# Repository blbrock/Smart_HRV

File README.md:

# Smart HRV  
Smart HRV replaces OEM controllers for Carrier (and probably Venmar and other brand) Heat Recovery Ventilation  
units.  Smart HRV adds intelligence to system controls using indoor and outdoor sensors to montior humidity and  
to manage humidity, fresh air, and odor control optimal performance. Smart HRV also integrates with fan and dehumidifier  
controls on Nest thermostats.  The system consists of an arduino-based control unit, one or more indoor humidity sensors.  
An outdoor temperature and humidity sensor, and an android user interface app to provide monitoring and control of system   
functions.  
  
The current system is customized to our own application and will likely need modification for other applications. But the   
package includes basic serial control logic for controlling an HRV and hopefully can provide guidance for others wishing  
to improve permormance of their heat recovery ventialation systems.  

# Background  
HRV and ERV (Energy Recovery Ventillator) have three basic functions:  
  
1. Manage indoor air quality efficiently by exchange fresh outdoor air for stale indoor air while recovering a portion of the heat from the exhaust airstream to conserve energy. 
 
2. Manage indoor humidity to reduce damage around windows and other cold surfaces by exchanging moist indoor air with dryer outdoor air; again recovering a portion of the heat from the exhaust air stream.  

3. Manage odors by exhausting indoor air.  
  
HRV/ERV systems work very well but the controls that came with ours (and most other units) fail on all three of their intended tasks.  Many units like ours lack any sort of timer circuit to allow fresh air exchange to be cycled. Instead, manufacturers and many HVAC expert claim the unit should be run continuously to maintain a steady flow of fresh air. This is insane! Heat recovery efficiency ranges from around 60%-70% for HRV units like ours, to about 90% for the newest ERV units. That means for every cubic foot of air exhausted by our unit, we lose 40% of the heat it contains. Heat we paid dearly to produce! Sure, it's better than opening a window but cycling the unit can provide plenty of fresh air while saving a significant amount of heat. Second, the best humidity to keep your house in winter depends on the outside temperature. The colder it is outside, the more likely moisture is to condense on windows so you need lower indoor humidity to prevent it. Also, the ability to reduce humidity by echanging indoor and outdoor air depends on the humidity outside. Luckily, outdoor humidity drops with the temperatue so on cold days, there is a good chance it is dryer outside than inside. But still, basic HRV units have no way to know if exchanging air will help and they could run in futility without reducing indoor humidity on wet days. Basic controllers have a manual dial setting to adjust the target indoor humidity. But outdoor temperatures fluctuate wildly over the day and season and nobody has the time to constantly fiddle with the dial to guess what the weather is going to do. This leads to settings that either run too little or too much so wind up with condensation damage on the windows anyway, wasted heat loss, or both. Finally, HRV/ERV units often include manual push buttons installed in bathrooms and laundry rooms that run for a set time when humidity or odor control is needed. OUrs ran for 20 minutes on a push which was not enough time to eliminate humidity after a shower, and certainly not enough time to eliminate odors when the relatives are visiting.

After years of frustration and some band-aid fixes for these inadequate controls, the catalyst to do something came when I purchased several Nest thermostats for our house and realized they provided fan and dehumidifier control functions that could improve the situation.  The fan control provided adjustable fresh air cycling and the dehumidifier provided the possibility of continuously monitoring outdoor temps and updating the humidity setpoint to always have the HRV trying to achieve the optimal humidity. I thought it would be just a matter of throwing in a couple of relays to get the Nest talking to the HRV but I was wrong.  There is no provision for such a setup so the only good option was to hack the controller.  So I set about reverse engineering the serial ttl communication logic, tossing out the old ugly wall controller and replacing it with an arduino controller interfaced with a cheap used android tablet mounted on the wall. The result is the Smart HRV system which has been chugging along with continuous tweaks for about two years now.

# Features: 

1. Monitors indoor humidity in multiple rooms and outdoor temperature and humidity to automatically and intelligently determine optimal inddor humidity levels and initiate fresh air exchange or recirculation cycles to achieve target humidity with minimal heat loss.

2. Integrates with Nest thermostat to allow fan controls on thermostat to initiate low speed air exchange cycles.

3. Defrost indicator on user interface to show when a defrost recirculating cycle is active.

4. Tracks cumulative run time and alerts users when it is time to service filters.  

# Extras:  

# Error checking and logging:   

# Known Bugs:

- The HRV unit may enter an error condition if someone manually presses a ventilation button in a bathroom while an automated dehumidification cycle is already in progress.  This appears to be due to some internal control logic within the HRV.  My work around is to power cycle the HRV unit if that happens to reset the error condition.  A better solution would be to wire the manual ventilation buttons directly to the arduino control panel and modify the control panel schematic and arduino sketch to bypass the internal HRV controller for handling manual ventilation requests.

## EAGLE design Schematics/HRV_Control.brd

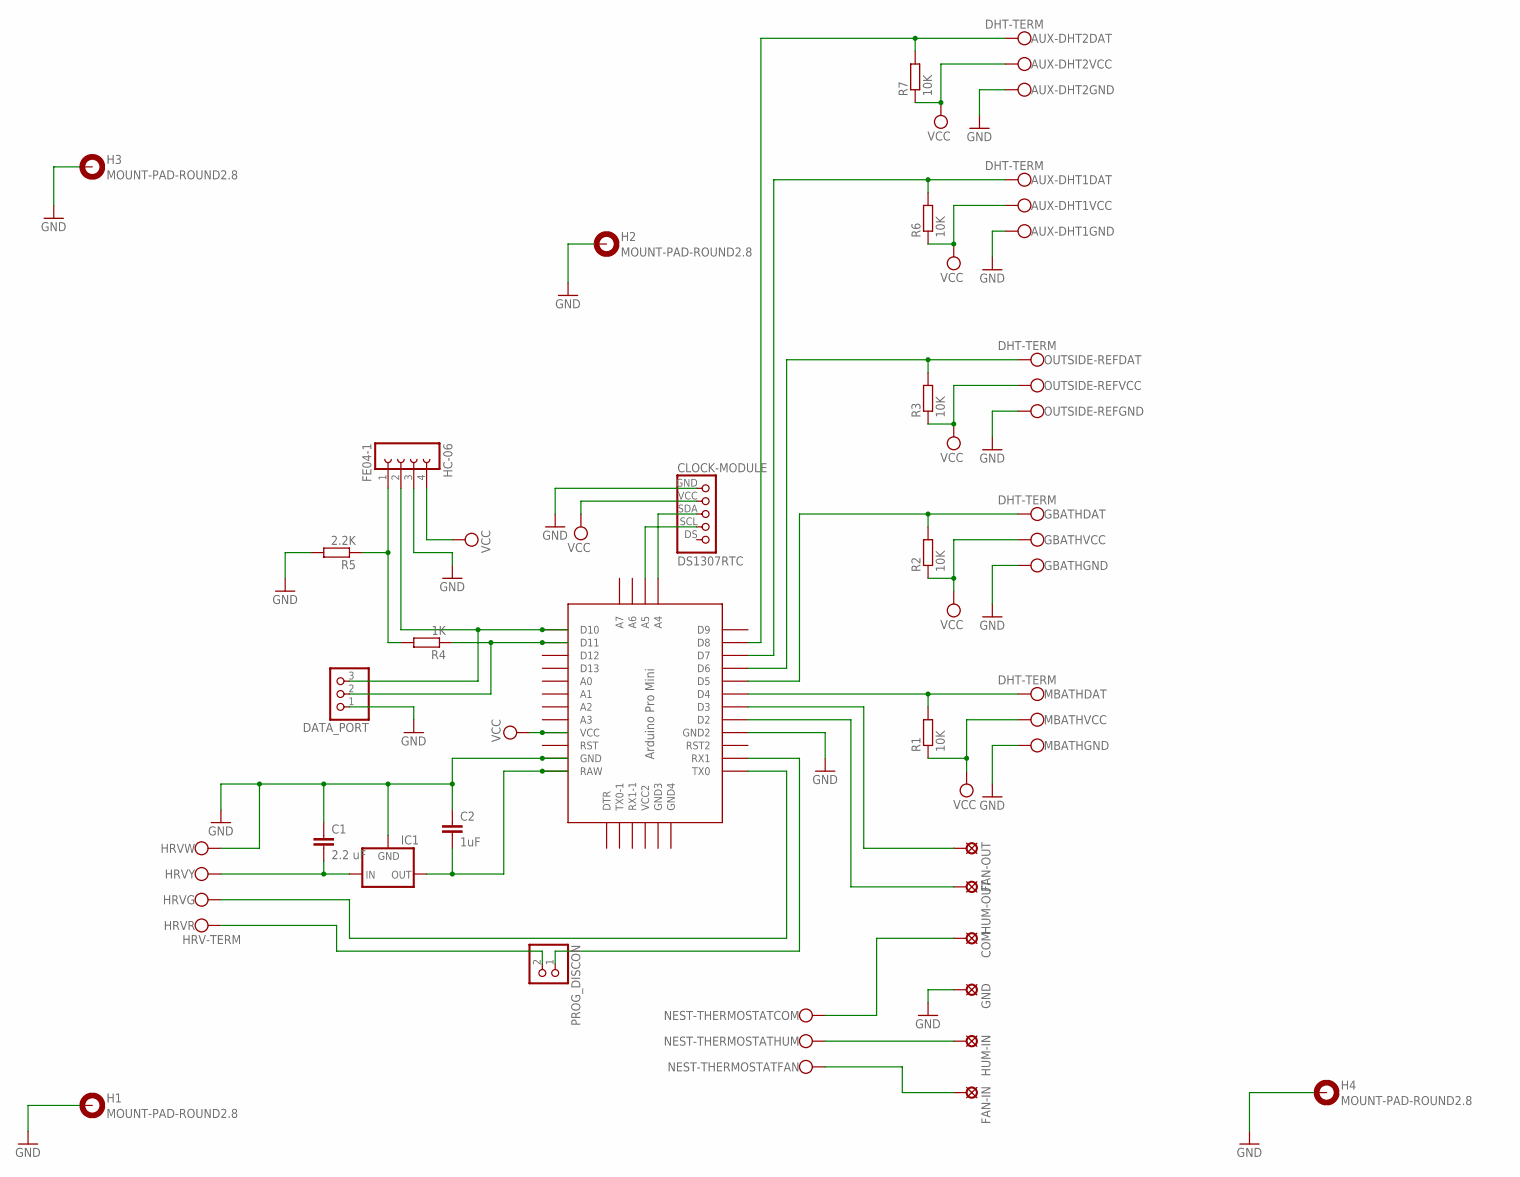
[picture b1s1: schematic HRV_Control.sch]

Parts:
AUX-DHT1, AUX-DHT2: DHT-TERM; DHT-TERMINAL
C1: 2.2 uF; C5B3
C2: 1uF; C025-024X044
CLOCK-MODULE: DS1307RTC
COM: SE14
DATA_PORT: PINHD-1X3; 1X03
FAN-IN: SE14
FAN-OUT: SE14
GBATH: DHT-TERM; DHT-TERMINAL
GND: SE14
H1, H2, H3, H4: MOUNT-PAD-ROUND2.8; 2,8-PAD
HC-06: FE04-1
HRV: HRV-TERM
HUM-IN: SE14
HUM-OUT: SE14
IC1: 78XXL
MBATH: DHT-TERM; DHT-TERMINAL
NEST-THERMOSTAT: NEST-TERM
OUTSIDE-REF: DHT-TERM; DHT-TERMINAL
PROG_DISCON: PINHD-1X2; 1X02
R1, R2, R3, R6, R7: 10K; 0204/7
R4: 1K; 0204/7
R5: 2.2K; 0204/7
U$6: PRO-MINI

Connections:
GND: AUX-DHT1.GND, AUX-DHT2.GND, C1.1, C2.1, CLOCK-MODULE.GND, DATA_PORT.1, GBATH.GND, GND.MP, H1.B2,8, H2.B2,8, H3.B2,8, H4.B2,8, HC-06.3, HRV.W, IC1.GND, MBATH.GND, OUTSIDE-REF.GND, R5.2, U$6.GND, U$6.GND1 (GND2)
unnamed: C1.2, HRV.Y, IC1.IN
unnamed: FAN-IN.MP, NEST-THERMOSTAT.FAN
unnamed: C2.2, IC1.OUT, U$6.RAW
unnamed: HRV.G, U$6.TX0
unnamed: PROG_DISCON.1, U$6.RX1
unnamed: MBATH.DAT, R1.2, U$6.D4
unnamed: HC-06.1, R4.2, R5.1
unnamed: HUM-IN.MP, NEST-THERMOSTAT.HUM
unnamed: COM.MP, NEST-THERMOSTAT.COM
unnamed: OUTSIDE-REF.DAT, R3.2, U$6.D6
unnamed: GBATH.DAT, R2.2, U$6.D5
unnamed: FAN-OUT.MP, U$6.D3
unnamed: HUM-OUT.MP, U$6.D2
unnamed: HRV.R, PROG_DISCON.2
unnamed: AUX-DHT1.DAT, R6.2, U$6.D7
unnamed: AUX-DHT2.DAT, R7.2, U$6.D8
SCL: CLOCK-MODULE.SCL, U$6.A5
SDA: CLOCK-MODULE.SDA, U$6.A4
SRX: DATA_PORT.2, R4.1, U$6.D11
STX: DATA_PORT.3, HC-06.2, U$6.D10
VCC: AUX-DHT1.VCC, AUX-DHT2.VCC, CLOCK-MODULE.VCC, GBATH.VCC, HC-06.4, MBATH.VCC, OUTSIDE-REF.VCC, R1.1, R2.1, R3.1, R6.1, R7.1, U$6.VCC

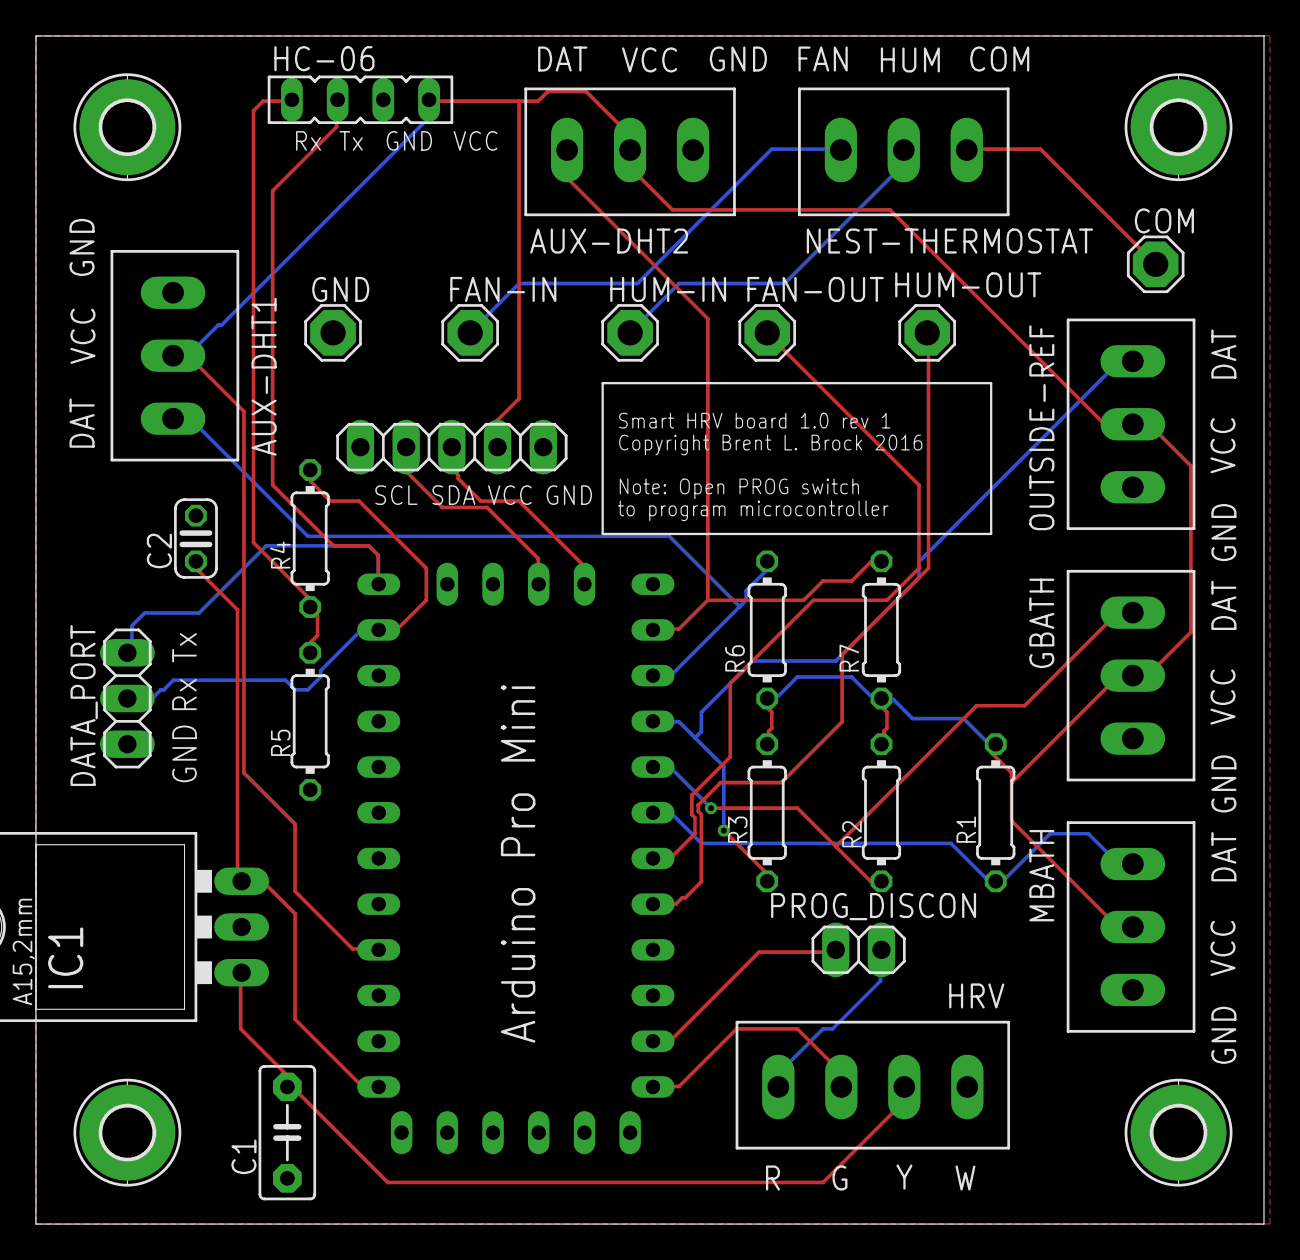
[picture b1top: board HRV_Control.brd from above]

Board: 2 copper layers, 68.2 x 66.0 mm, 32 parts (0 on the bottom side), 22 nets.

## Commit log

2016-10-11 :neckbeard: Added .gitattributes & .gitignore files
2016-10-11 Initial Upload
2016-10-11 Add cold weather override
    Suppresses fresh air exchange if outside temperature is < 15F.
2016-10-11 Rename sketch file
    Renamed file to be able to open it with Arduino IDE
2016-10-12 Adjust dehumidify setpoint
    Adjusted dehumidify off trigger to prevent overrun times in
    recirculation mode.
2016-10-22 Check Humidity update
    Cleaned up code for more efficient processing and readability.
2016-11-02 Update .ignore file
2016-11-02 Check Humidity update
    - added max temp parameter to prevent fresh air exchange during
    extremely cold weather
    - simplified Check_Humidity code for more efficient execution and
    readability
    - set recirculation mode as default for dehumidification to reduce heat
    loss
2016-11-22 Misc. enhancements
    - Revised algorithms for fresh air and dehumidification for improved
    efficiency.
    - Added ClearEeprom function initiatated by sending code 5 from to
    microprocessor.
    - Revised circuit board to fix errors with voltage regulator pinout and
    resistor sizes.
2016-11-22 Bug fix
    Fixed bug preventing HRV from going to fresh air exchange when target
    humidity < minimum indoor humidity.
2016-11-26 Fixed manual override
    - Changed manual command processing to prevent automation commands from
    overriding manual commands. Now manual commands sent from the control
    panel cause the processor to suspend processing of automated control
    commands until an Off (236) command is recieved, or four hours has
    elapsed since a manual command was issued.
    - Made minor adjustments to fresh air processing to improve efficiency.
2016-12-08 Minor bug fixes
2016-12-17 Enhancements
    humidity monitored as rolling average to smooth response
2019-05-14 Several small updates
2019-05-14 add image file
2019-05-14 Added USART commands
    Added documentation of control logic signals discovered during reverse engineering.
2019-05-14 bug report
2019-05-14 Upadate readme

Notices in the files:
Schematics/HRV_Control.brd:
Copyright Brent L. Brock 2016
